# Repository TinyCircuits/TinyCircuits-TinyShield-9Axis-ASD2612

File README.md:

# TinyCircuits TinyShield 9-Axis Board
# ASD2612 Rev3

WARNING: This repo is obsolete, the current 9-Axis TinyShield has been moved to the Combo Sensor TinyShield repo found here: https://github.com/TinyCircuits/TinyCircuits-TinyShield-Sensor-ASD2511

These are the design files for the TinyCircuits ASD2612 Rev 3 PCB.  This is a TinyShield board (20mm x 20mm) that has a 9-Axis IMU.

Format is in Cadsoft Eagle format - Eagle version 6.2 was used for the original design.

# License:

Design by TinyCircuits.
All design files are released under the Creative Commons Attribution Share-Alike 3.0 License, see the following link for details: http://creativecommons.org/licenses/by-sa/3.0

All text above must be included in any redistribution or derived design

This project uses designs and concepts developed as part of the Arduino project and the LilyPad project.  The TinyCircuits design files themselves (schematics, PCB and libraries) are not directly derived from these works' design files and have been created new, however the concepts and basic architecture behind the TinyDuino and TinyLily products are derived and we thank the hard work of the organizations below for their contributions to open-source hardware:
  
Original Arduino Uno Design by Team Arduino

LilyPad Arduino Design by Leah Buechley and Sparkfun Electronics

Please support the open-source hardware community

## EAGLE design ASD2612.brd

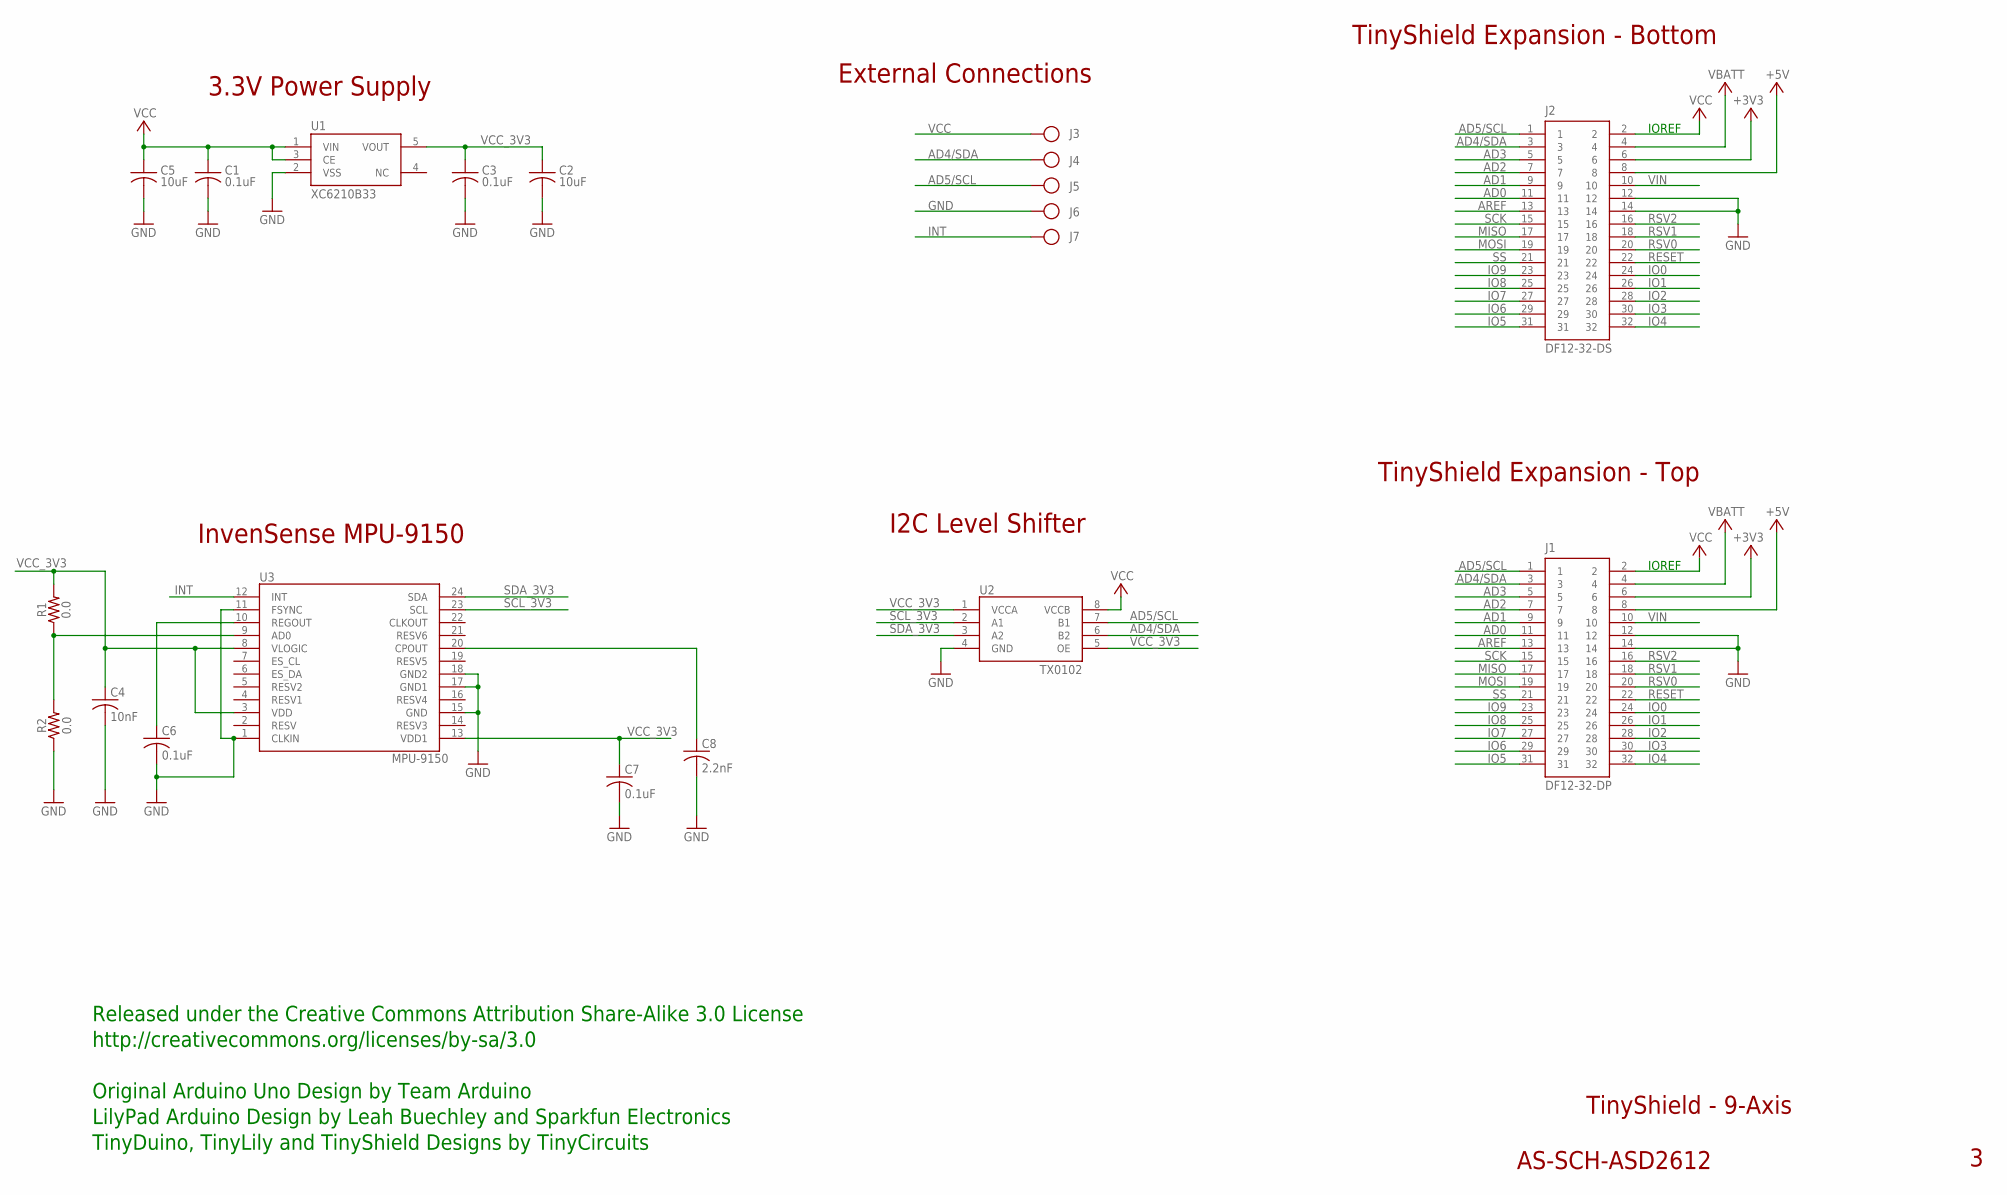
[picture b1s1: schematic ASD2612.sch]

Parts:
C1, C3: 0.1uF; C0402; PARTNO AS-ITM-00008
C2: 10uF; C0805; PARTNO AS-ITM-00045
C4: 10nF; C0402
C5: 10uF; C0805
C6, C7: 0.1uF; C0402
C8: 2.2nF; C0402
J1: DF12-32-DP; PARTNO AS-ITM-00015
J2: DF12-32-DS; PARTNO AS-ITM-00012
J3, J4, J5, J6, J7: PIN_1X.1"; 1X.1"
R1: 0.0; 0402
R2: AS-ITM-000760402_SHORT; 0402_SHORT
U1: XC6210B33; SOT-25
U2: TX0102; DQE(R-PX2SON-N8)
U3: MPU-9150

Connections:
+3V3: J1.6, J2.6
+5V: J1.8, J2.8
AD0: J1.11, J2.11
AD1: J1.9, J2.9
AD2: J1.7, J2.7
AD3: J1.5, J2.5
AD4/SDA: J1.3, J2.3, J4.1, U2.6 (B2)
AD5/SCL: J1.1, J2.1, J5.1, U2.7 (B1)
AREF: J1.13, J2.13
GND: C1.2, C2.2, C3.2, C4.2, C5.2, C6.2, C7.2, C8.2, J1.12, J1.14, J2.12, J2.14, J6.1, R2.1, U1.2 (VSS), U2.4 (GND), U3.1 (CLKIN), U3.11 (FSYNC), U3.15 (GND), U3.17 (GND1), U3.18 (GND2)
INT: J7.1, U3.12 (INT)
IO0: J1.24, J2.24
IO1: J1.26, J2.26
IO2: J1.28, J2.28
IO3: J1.30, J2.30
IO4: J1.32, J2.32
IO5: J1.31, J2.31
IO6: J1.29, J2.29
IO7: J1.27, J2.27
IO8: J1.25, J2.25
IO9: J1.23, J2.23
MISO: J1.17, J2.17
MOSI: J1.19, J2.19
unnamed: C8.1, U3.20 (CPOUT)
unnamed: C6.1, U3.10 (REGOUT)
unnamed: R1.1, R2.2, U3.9 (AD0)
RESET: J1.22, J2.22
RSV0: J1.20, J2.20
RSV1: J1.18, J2.18
RSV2: J1.16, J2.16
SCK: J1.15, J2.15
SCL_3V3: U2.2 (A1), U3.23 (SCL)
SDA_3V3: U2.3 (A2), U3.24 (SDA)
SS: J1.21, J2.21
VBATT: J1.4, J2.4
VCC: C1.1, C5.1, J1.2, J2.2, J3.1, U1.1 (VIN), U1.3 (CE), U2.8 (VCCB)
VCC_3V3: C2.1, C3.1, C4.1, C7.1, R1.2, U1.5 (VOUT), U2.1 (VCCA), U2.5 (OE), U3.3 (VDD), U3.8 (VLOGIC), U3.13 (VDD1)
VIN: J1.10, J2.10

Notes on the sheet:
TinyShield Expansion - Bottom
TinyShield - 9-Axis
AS-SCH-ASD2612
TinyShield Expansion - Top
IOREF
Released under the Creative Commons Attribution Share-Alike 3.0 License
http://creativecommons.org/licenses/by-sa/3.0
LilyPad Arduino Design by Leah Buechley and Sparkfun Electronics
TinyDuino, TinyLily and TinyShield Designs by TinyCircuits
Original Arduino Uno Design by Team Arduino
External Connections
3.3V Power Supply
I2C Level Shifter
InvenSense MPU-9150
0.0

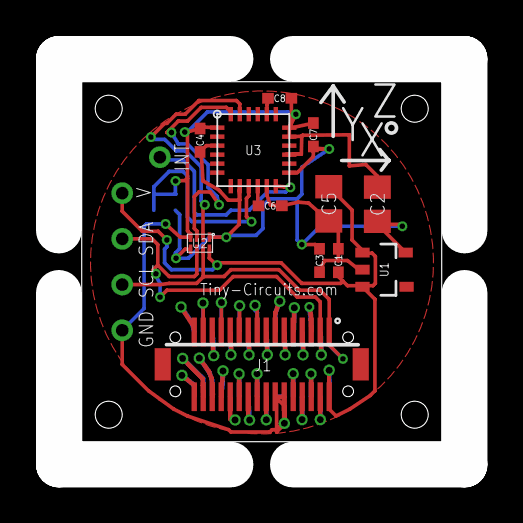
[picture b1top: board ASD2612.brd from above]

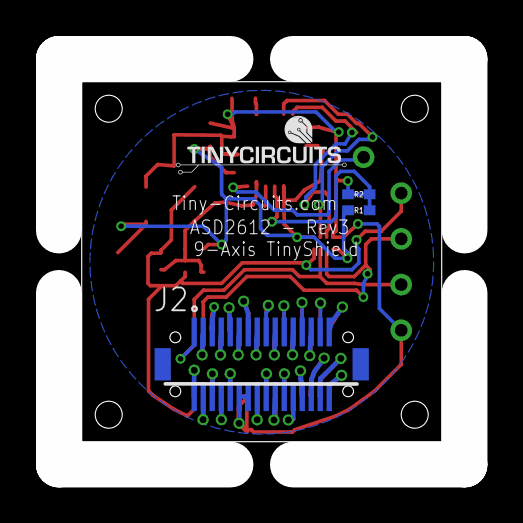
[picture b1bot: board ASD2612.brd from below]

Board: 2 copper layers, 20.0 x 20.0 mm, 21 parts (3 on the bottom side), 38 nets.

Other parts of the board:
U$1: DOCFIELD-TINYCIRCUITS-PCB

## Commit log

2019-01-08 removed example
